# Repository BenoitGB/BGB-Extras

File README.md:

#  BGB - Extras
Extra electronics, software and C.A.D projects. You can see some examples hereunder.

## Extra Computer Aided Design

Some spare parts are available :  

<table ><tr><td width="800px">
	
	<h4>Mecano C876 (custom)</h4>
	Wheel for Mecano, made by using revolution approach.
</td></tr></table>

<table ><tr><td width="800px">
	
	<h4>Mater Head by Mega Blocks</h4>
	Made under "Blender" using "Bevel" function.
</td></tr></table>

<table ><tr><td width="800px">
	
	<h4>CAME key</h4>
	Can be useful in case of power cut. Made of 2 bodies.
</td></tr></table>

## Extra Softwares

Training projects in many languages, including projects made during personal
["OpenClassRoom"](https://openclassrooms.com/) lessons.

<table ><tr><td width="800px">

<h4>Sorting Demo</h4>
<p>
A <strong>Qt</strong> CrossCompile project for <strong>Android </strong>.
Using  <strong>QCharts</strong> and  <strong>QThread </strong> to show up sorting algorithm process.
This project refers to strategy patterns for sorting methods (Sorting Strategy).
</p>

</td></tr></table>

<table ><tr><td width="800px">

<h4>BGB-Filmothek</h4>
A <strong>Angular</strong> Project made for <a hrfe="https://openclassrooms.com/fr/courses/4668271-developpez-des-applications-web-avec-angulardeveloppez-des-applications-web-avec-angular">
"Développez des applications Web avec Angular" </a> an OpenClassRoom lesson.
</td></tr></table>

## Extra Electronics

Little electronics projects for railway scales models or whatever stuff which can be useful.

<table ><tr><td width="800px">
	
	<h4>Dcc NEM652 Socket</h4>
	This is an 8-pin socket connector standard for DCC decoder.
</td></tr></table>

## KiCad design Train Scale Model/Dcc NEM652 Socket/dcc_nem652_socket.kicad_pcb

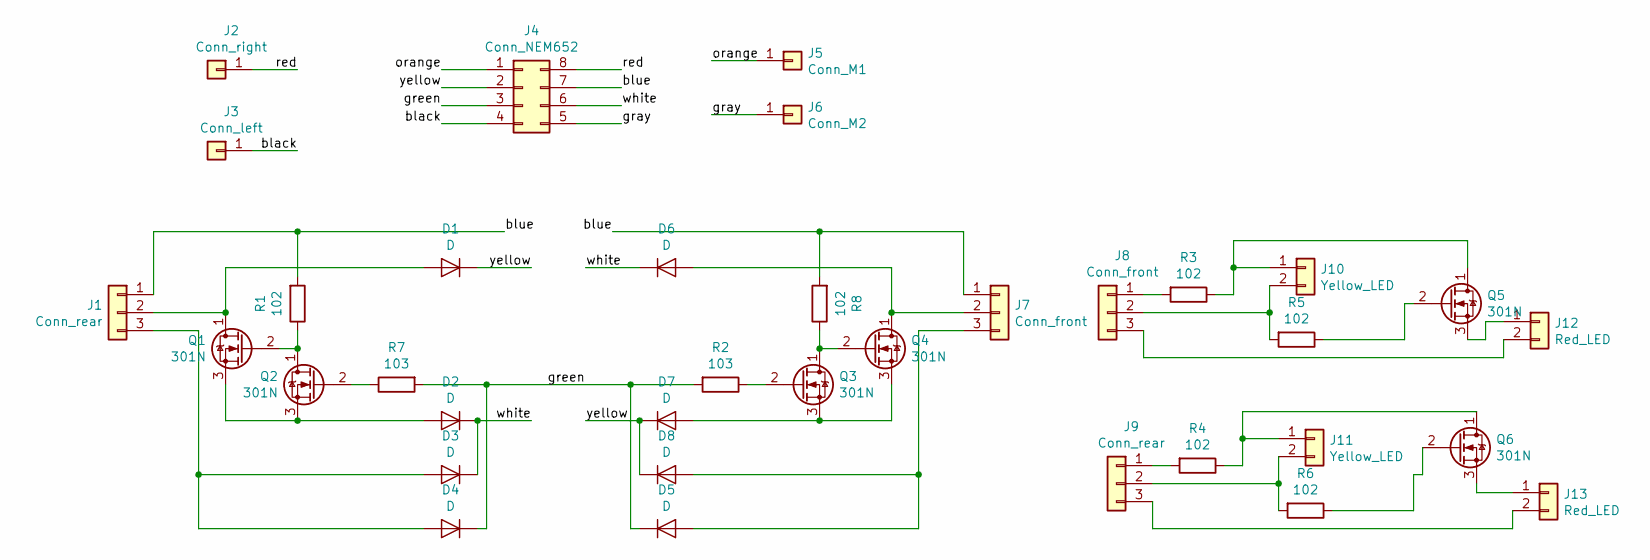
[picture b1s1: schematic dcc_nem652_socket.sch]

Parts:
D1, D2, D3, D4, D5, D6, D7, D8: D; D_2010_5025Metric_Pad1.52x2.65mm_HandSolder
J1, J9: Conn_rear; PinSocket_1x03_P2.54mm_Vertical
J2: Conn_right; PinSocket_1x01_P2.54mm_Vertical
J3: Conn_left; PinSocket_1x01_P2.54mm_Vertical
J4: Conn_NEM652; PinSocket_2x04_P2.54mm_Vertical
J5: Conn_M1; PinSocket_1x01_P2.54mm_Vertical
J6: Conn_M2; PinSocket_1x01_P2.54mm_Vertical
J7, J8: Conn_front; PinSocket_1x03_P2.54mm_Vertical
J10, J11: Yellow_LED; PinSocket_2x01_P2.54mm_Vertical
J12, J13: Red_LED; PinSocket_2x01_P2.54mm_Vertical
Q1, Q2, Q3, Q4, Q5, Q6: 301N; SOT-23
R1, R3, R4, R5, R6, R8: 102; R_2010_5025Metric_Pad1.52x2.65mm_HandSolder
R2, R7: 103; R_2010_5025Metric_Pad1.52x2.65mm_HandSolder

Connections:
/black: J3.1, J4.4
/blue: J1.1, J4.7, J7.1, R1.2, R8.2
/gray: J4.5, J6.1
/green: D4.1 (K), D5.1 (K), J4.3, R2.2, R7.2
/orange: J4.1, J5.1
/red: J2.1, J4.8
/white: D2.1 (K), D3.1 (K), D6.1 (K), J4.6
/yellow: D1.1 (K), D7.1 (K), D8.1 (K), J4.2
unnamed: D1.2 (A), J1.2, Q1.1 (D)
unnamed: D2.2 (A), Q1.3 (S), Q2.3 (S)
unnamed: D3.2 (A), D4.2 (A), J1.3
unnamed: D5.2 (A), D8.2 (A), J7.3
unnamed: D6.2 (A), J7.2, Q4.1 (D)
unnamed: D7.2 (A), Q3.3 (S), Q4.3 (S)
unnamed: J8.1, R3.2
unnamed: J9.1, R4.2
unnamed: J10.1, Q5.1 (D), R3.1
unnamed: J8.2, J10.2, R5.2
unnamed: J11.1, Q6.1 (D), R4.1
unnamed: J9.2, J11.2, R6.2
unnamed: J12.1, Q5.3 (S)
unnamed: J8.3, J12.2
unnamed: J13.1, Q6.3 (S)
unnamed: J9.3, J13.2
unnamed: Q1.2 (G), Q2.1 (D), R1.1
unnamed: Q2.2 (G), R7.1
unnamed: Q3.1 (D), Q4.2 (G), R8.1
unnamed: Q3.2 (G), R2.1
unnamed: Q5.2 (G), R5.1
unnamed: Q6.2 (G), R6.1

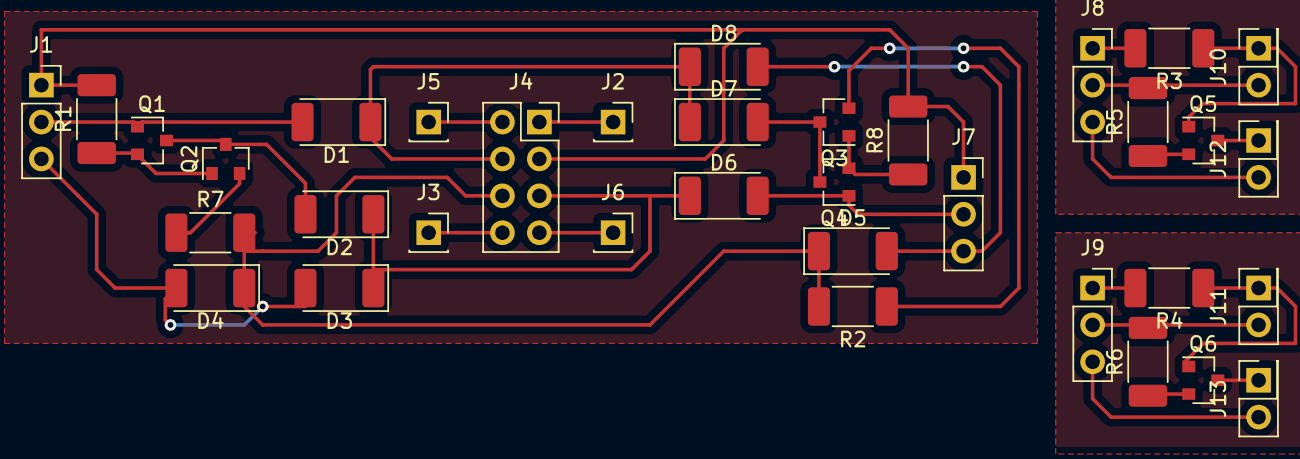
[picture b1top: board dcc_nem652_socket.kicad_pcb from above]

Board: 2 copper layers, 35 parts (0 on the bottom side), 30 nets.

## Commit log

2020-03-04 General Commit of Extra stuffs
2020-03-04 Add forgotten file
2020-03-06 add "dcc NEM652 Socket"
2021-01-08 Add ReadMe
2021-01-08 set GFM compatible
2025-08-24 change logo
